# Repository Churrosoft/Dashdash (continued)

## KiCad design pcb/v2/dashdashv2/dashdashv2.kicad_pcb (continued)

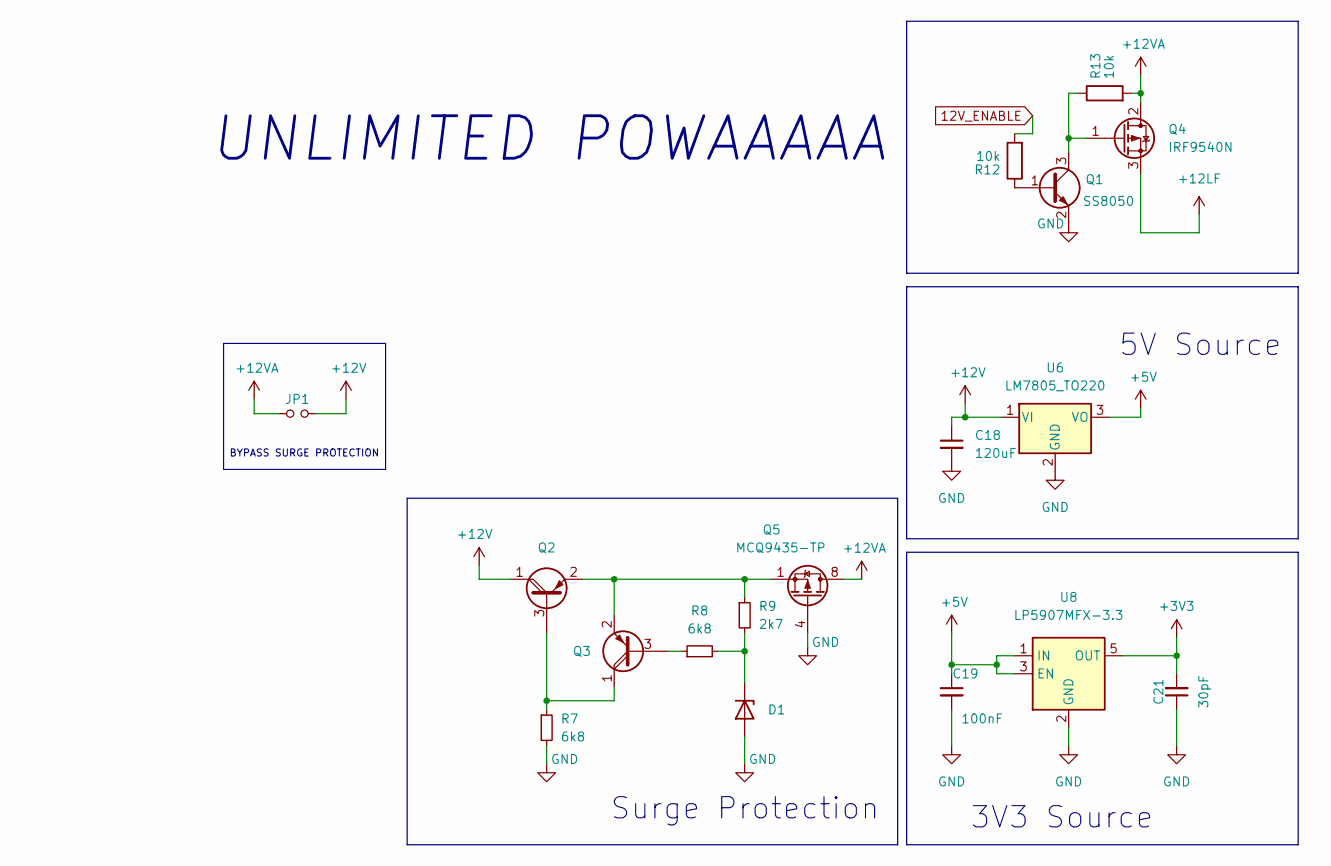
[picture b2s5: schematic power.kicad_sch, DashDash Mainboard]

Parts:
C18: 120uF; CP_Elec_8x6.5
C19: 100nF; C_0603_1608Metric
C21: 30pF; C_0603_1608Metric
D1: BZX84C5V6LT1G; SOT-23
JP1: Jumper_NO_Small; SolderJumper-2_P1.3mm_Open_RoundedPad1.0x1.5mm
Q1: SS8050; SOT-23; LCSC C2150
Q2, Q3: 2PB1424,115; SOT-89-3
Q4: IRF9540N; TO-252-2
Q5: MCQ9435-TP; SOIC-8_3.9x4.9mm_P1.27mm
R7, R8: 6k8; R_0603_1608Metric
R9: 2k7; R_0603_1608Metric
R12, R13: 10k; R_0603_1608Metric
U6: LM7805_TO220; TO-220-3_Vertical
U8: LP5907MFX-3.3; SOT-23-5

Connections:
12V_BATT: JP1.1, Q4.2 (D), Q5.5 (D), Q5.6 (D), Q5.7 (D), Q5.8 (D), R13.2; also elsewhere on the board
12V_ENABLE: R12.2; also elsewhere on the board
+3V3: C21.2, U8.5 (OUT); also elsewhere on the board
+5V: C19.1, U6.3 (VO), U8.1 (IN), U8.3 (EN); also elsewhere on the board
+12LF: Q4.3 (S); also elsewhere on the board
+12V: C18.1, JP1.2, Q2.1 (C), U6.1 (VI); also elsewhere on the board
GND: C18.2, C19.2, C21.1, D1.1 (A), Q1.2 (E), Q5.4 (G), R7.2, U6.2 (GND), U8.2 (GND); also elsewhere on the board
unnamed: D1.3 (K), R8.2, R9.2
unnamed: Q1.1 (B), R12.1
unnamed: Q1.3 (C), Q4.1 (G), R13.1
unnamed: Q2.2 (E), Q3.2 (E), Q5.1 (S), Q5.2 (S), Q5.3 (S), R9.1
unnamed: Q2.3 (B), Q3.1 (C), R7.1
unnamed: Q3.3 (B), R8.1

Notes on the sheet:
BYPASS SURGE PROTECTION
UNLIMITED POWAAAAA
5V Source
Surge Protection
3V3 Source

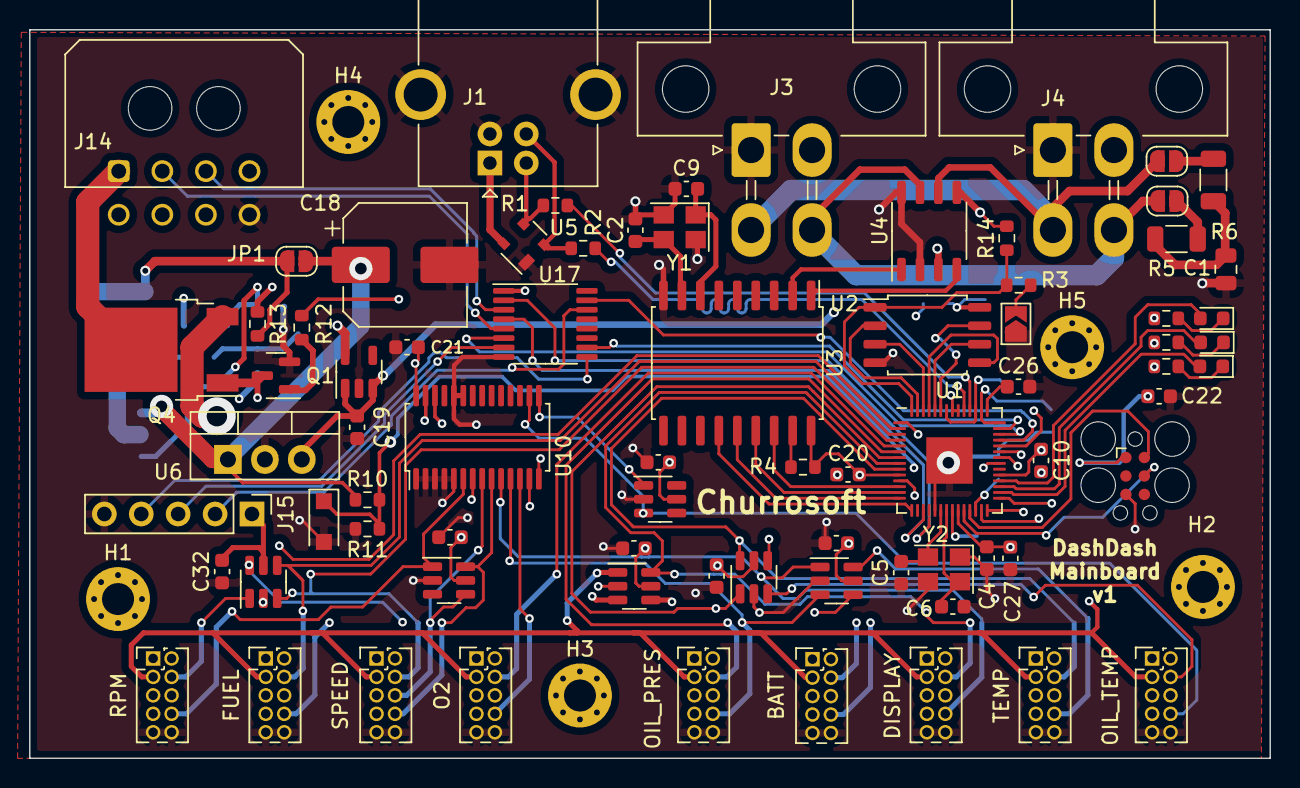
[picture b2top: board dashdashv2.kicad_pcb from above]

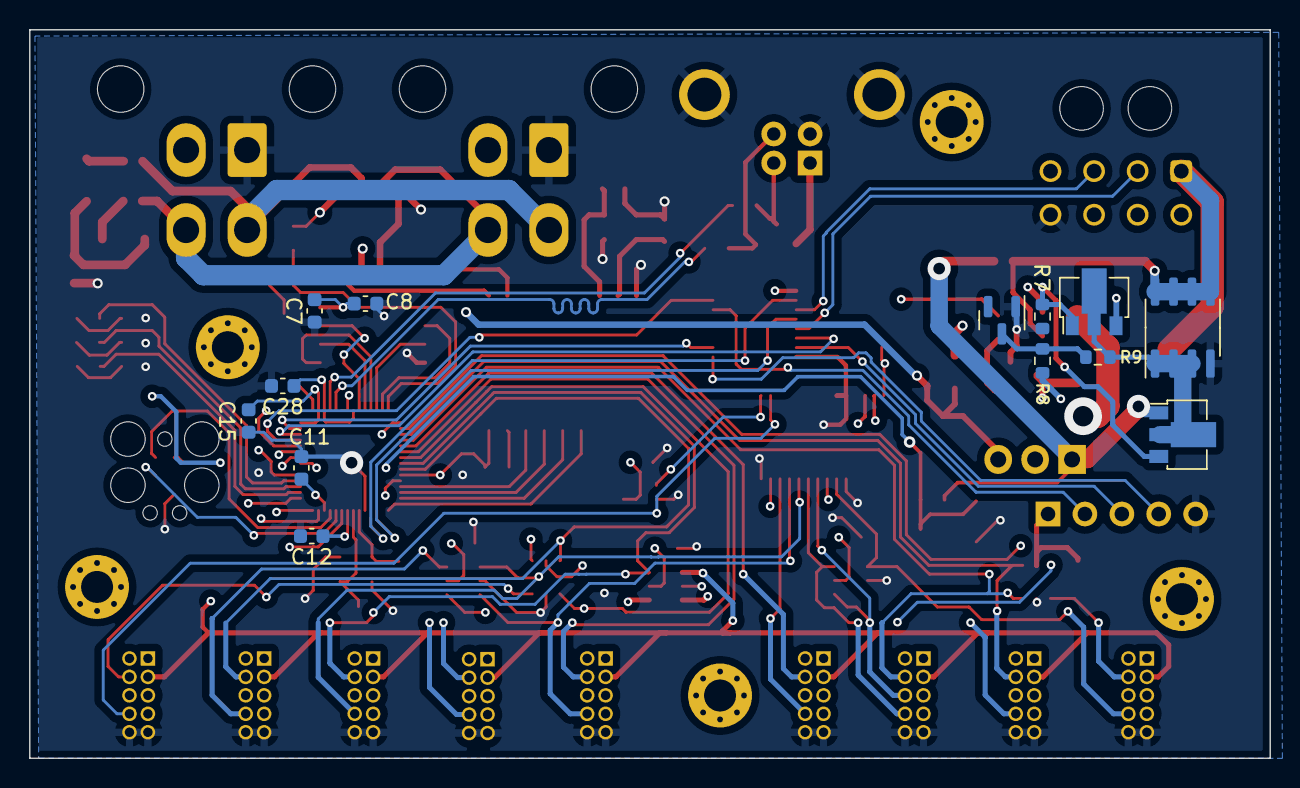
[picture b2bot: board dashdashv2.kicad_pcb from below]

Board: 4 copper layers, 85.4 x 50.1 mm, 94 parts (13 on the bottom side), 86 nets.

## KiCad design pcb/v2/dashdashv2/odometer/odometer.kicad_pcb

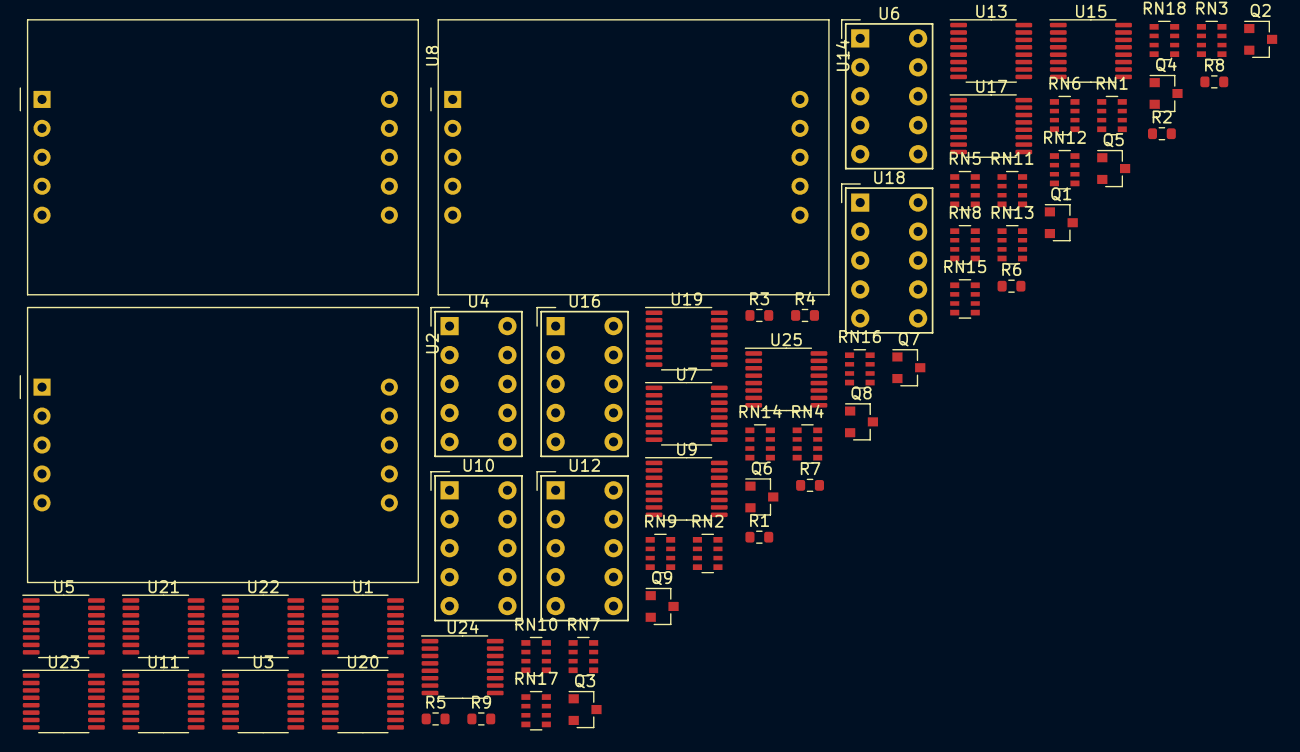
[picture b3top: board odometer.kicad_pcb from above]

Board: 2 copper layers, 61 parts (0 on the bottom side), 210 nets, no tracks yet.

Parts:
Q1, Q2, Q3, Q4, Q5, Q6, Q7, Q8, Q9: BSS138; SOT-23
R1, R2, R3, R4, R5, R6, R7, R8, R9: 1k 1/10W +-1%; R_0603_1608Metric
RN1, RN2, RN3, RN4, RN5, RN6, RN7, RN8, RN9, RN10, RN11, RN12, RN13, RN14, RN15, RN16, RN17, RN18: 560Ω ±5% 63mW; R_Array_Convex_4x0603
U1, U3, U5, U7, U9, U11, U13, U15, U17: 4511; TSSOP-16_4.4x5mm_P0.65mm
U2, U8, U14: HDSP-7801; SA15-11xxx
U4, U6, U10, U12, U16, U18: HDSP-7801
U19, U20, U21, U22, U23, U24, U25: 74HC595; TSSOP-16_4.4x5mm_P0.65mm

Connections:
+12V: U1.16 (Vdd), U3.16 (Vdd), U5.16 (Vdd), U7.16 (Vdd), U9.16 (Vdd), U11.16 (Vdd), U13.16 (Vdd), U15.16 (Vdd), U17.16 (Vdd), U19.16 (VCC), U20.16 (VCC), U21.16 (VCC), U22.16 (VCC), U23.16 (VCC), U24.16 (VCC), U25.16 (VCC)
/OE: U19.13 (~OE), U20.13 (~OE), U21.13 (~OE), U22.13 (~OE), U23.13 (~OE), U24.13 (~OE), U25.13 (~OE)
/PWM_OD: R2.1, R3.1, R5.1, R6.1, R8.1, R9.1
/PWM_VEL: R1.1, R4.1, R7.1
/RCLK: U19.12 (RCLK), U20.12 (RCLK), U21.12 (RCLK), U22.12 (RCLK), U23.12 (RCLK), U24.12 (RCLK), U25.12 (RCLK)
/SER: U19.9 (QH'), U19.14 (SER), U20.9 (QH'), U20.14 (SER), U21.9 (QH'), U21.14 (SER), U22.9 (QH'), U22.14 (SER), U23.9 (QH'), U23.14 (SER), U24.9 (QH'), U24.14 (SER), U25.14 (SER)
/SRCLK: U19.11 (SRCLK), U20.11 (SRCLK), U21.11 (SRCLK), U22.11 (SRCLK), U23.11 (SRCLK), U24.11 (SRCLK), U25.11 (SRCLK)
/SRCLR: U19.10 (~SRCLR), U20.10 (~SRCLR), U21.10 (~SRCLR), U22.10 (~SRCLR), U23.10 (~SRCLR), U24.10 (~SRCLR), U25.10 (~SRCLR)
/S_7S_A_BI: U1.4 (~BI), U24.1 (QB)
/S_7S_A_DA: U1.7 (DA), U23.4 (QE)
/S_7S_A_DB: U1.1 (DB), U23.5 (QF)
/S_7S_A_DC: U1.2 (DC), U23.6 (QG)
/S_7S_A_DD: U1.6 (DD), U23.7 (QH)
/S_7S_A_LT: U1.3 (~LT), U24.15 (QA)
/S_7S_B_BI: U7.4 (~BI), U13.4 (~BI), U24.7 (QH), U25.5 (QF)
/S_7S_B_DA: U7.7 (DA), U13.7 (DA), U24.2 (QC), U25.15 (QA)
/S_7S_B_DB: U7.1 (DB), U13.1 (DB), U24.3 (QD), U25.1 (QB)
/S_7S_B_DC: U7.2 (DC), U13.2 (DC), U24.4 (QE), U25.2 (QC)
/S_7S_B_DD: U7.6 (DD), U13.6 (DD), U24.5 (QF), U25.3 (QD)
/S_7S_B_LT: U7.3 (~LT), U13.3 (~LT), U24.6 (QG), U25.4 (QE)
/S_7S_D_1_A: U15.7 (DA), U19.15 (QA)
/S_7S_D_1_B: U15.1 (DB), U19.1 (QB)
/S_7S_D_1_BI: U15.4 (~BI), U19.5 (QF)
/S_7S_D_1_C: U15.2 (DC), U19.2 (QC)
/S_7S_D_1_D: U15.6 (DD), U19.3 (QD)
/S_7S_D_1_LT: U15.3 (~LT), U19.4 (QE)
/S_7S_D_2_A: U5.7 (DA), U19.6 (QG)
/S_7S_D_2_B: U5.1 (DB), U19.7 (QH)
/S_7S_D_2_BI: U5.4 (~BI), U20.3 (QD)
/S_7S_D_2_C: U5.2 (DC), U20.15 (QA)
/S_7S_D_2_D: U5.6 (DD), U20.1 (QB)
/S_7S_D_2_LT: U5.3 (~LT), U20.2 (QC)
/S_7S_D_3_A: U3.7 (DA), U20.4 (QE)
/S_7S_D_3_B: U3.1 (DB), U20.5 (QF)
/S_7S_D_3_BI: U3.4 (~BI), U21.1 (QB)
/S_7S_D_3_C: U3.2 (DC), U20.6 (QG)
/S_7S_D_3_D: U3.6 (DD), U20.7 (QH)
/S_7S_D_3_LT: U3.3 (~LT), U21.15 (QA)
/S_7S_D_4_A: U9.7 (DA), U21.2 (QC)
/S_7S_D_4_B: U9.1 (DB), U21.3 (QD)
/S_7S_D_4_BI: U9.4 (~BI), U21.7 (QH)
/S_7S_D_4_C: U9.2 (DC), U21.4 (QE)
/S_7S_D_4_D: U9.6 (DD), U21.5 (QF)
/S_7S_D_4_LT: U9.3 (~LT), U21.6 (QG)
/S_7S_D_5_A: U11.7 (DA), U22.15 (QA)
/S_7S_D_5_B: U11.1 (DB), U22.1 (QB)
/S_7S_D_5_BI: U11.4 (~BI), U22.5 (QF)
/S_7S_D_5_C: U11.2 (DC), U22.2 (QC)
/S_7S_D_5_D: U11.6 (DD), U22.3 (QD)
/S_7S_D_5_LT: U11.3 (~LT), U22.4 (QE)
/S_7S_D_6_A: U17.7 (DA), U22.6 (QG)
/S_7S_D_6_B: U17.1 (DB), U22.7 (QH)
/S_7S_D_6_BI: U17.4 (~BI), U23.3 (QD)
/S_7S_D_6_C: U17.2 (DC), U23.15 (QA)
/S_7S_D_6_D: U17.6 (DD), U23.1 (QB)
/S_7S_D_6_LT: U17.3 (~LT), U23.2 (QC)
GND: Q1.2 (S), Q2.2 (S), Q3.2 (S), Q4.2 (S), Q5.2 (S), Q6.2 (S), Q7.2 (S), Q8.2 (S), Q9.2 (S), RN11.8 (R1.2), U1.5 (~EL), U1.8 (Vss), U3.5 (~EL), U3.8 (Vss), U5.5 (~EL), U5.8 (Vss), U7.5 (~EL), U7.8 (Vss), U9.5 (~EL), U9.8 (Vss), U11.5 (~EL), U11.8 (Vss), U13.5 (~EL), U13.8 (Vss), U15.5 (~EL), U15.8 (Vss), U17.5 (~EL), U17.8 (Vss), U19.8 (GND), U20.8 (GND), U21.8 (GND), U22.8 (GND), U23.8 (GND), U24.8 (GND), U25.8 (GND)
unnamed: Q1.1 (G), R1.2
unnamed: Q1.3 (D), U2.1 (CA), U2.6 (CA)
unnamed: Q2.1 (G), R2.2
unnamed: Q2.3 (D), U4.1 (CA), U4.6 (CA)
unnamed: Q3.1 (G), R3.2
unnamed: Q3.3 (D), U6.1 (CA), U6.6 (CA)
unnamed: Q4.1 (G), R4.2
unnamed: Q4.3 (D), U8.1 (CA), U8.6 (CA)
unnamed: Q5.1 (G), R5.2
unnamed: Q5.3 (D), U10.1 (CA), U10.6 (CA)
unnamed: Q6.1 (G), R6.2
unnamed: Q6.3 (D), U12.1 (CA), U12.6 (CA)
unnamed: Q7.1 (G), R7.2
unnamed: Q7.3 (D), U14.1 (CA), U14.6 (CA)
unnamed: Q8.1 (G), R8.2
unnamed: Q8.3 (D), U16.1 (CA), U16.6 (CA)
unnamed: Q9.1 (G), R9.2
unnamed: Q9.3 (D), U18.1 (CA), U18.6 (CA)
unnamed: RN1.1 (R1.1), U2.5 (D)
unnamed: RN1.2 (R2.1), U2.8 (C)
unnamed: RN1.3 (R3.1), U2.9 (B)
unnamed: RN1.4 (R4.1), U2.10 (A)
unnamed: RN1.5 (R4.2), U1.13 (Qa)
unnamed: RN1.6 (R3.2), U1.12 (Qb)
unnamed: RN1.7 (R2.2), U1.11 (Qc)
unnamed: RN1.8 (R1.2), U1.10 (Qd)
unnamed: RN2.1 (R1.1), U4.5 (D)
unnamed: RN2.2 (R2.1), U4.8 (C)
unnamed: RN2.3 (R3.1), U4.9 (B)
unnamed: RN2.4 (R4.1), U4.10 (A)
unnamed: RN2.5 (R4.2), U3.13 (Qa)
unnamed: RN2.6 (R3.2), U3.12 (Qb)
unnamed: RN2.7 (R2.2), U3.11 (Qc)
unnamed: RN2.8 (R1.2), U3.10 (Qd)
unnamed: RN3.1 (R1.1), U6.5 (D)
unnamed: RN3.2 (R2.1), U6.8 (C)
unnamed: RN3.3 (R3.1), U6.9 (B)
unnamed: RN3.4 (R4.1), U6.10 (A)
unnamed: RN3.5 (R4.2), U5.13 (Qa)
unnamed: RN3.6 (R3.2), U5.12 (Qb)
unnamed: RN3.7 (R2.2), U5.11 (Qc)
unnamed: RN3.8 (R1.2), U5.10 (Qd)
unnamed: RN4.1 (R1.1), U2.7 (DP)
unnamed: RN4.2 (R2.1), U2.3 (G)
unnamed: RN4.3 (R3.1), U2.2 (F)
unnamed: RN4.4 (R4.1), U2.4 (E)
unnamed: RN4.5 (R4.2), U1.9 (Qe)
unnamed: RN4.6 (R3.2), U1.15 (Qf)
unnamed: RN4.7 (R2.2), U1.14 (Qg)
unnamed: RN5.1 (R1.1), U4.7 (DP)
unnamed: RN5.2 (R2.1), U4.3 (G)
unnamed: RN5.3 (R3.1), U4.2 (F)
unnamed: RN5.4 (R4.1), U4.4 (E)
unnamed: RN5.5 (R4.2), U3.9 (Qe)
unnamed: RN5.6 (R3.2), U3.15 (Qf)
unnamed: RN5.7 (R2.2), U3.14 (Qg)
unnamed: RN6.1 (R1.1), U6.7 (DP)
unnamed: RN6.2 (R2.1), U6.3 (G)
unnamed: RN6.3 (R3.1), U6.2 (F)
unnamed: RN6.4 (R4.1), U6.4 (E)
unnamed: RN6.5 (R4.2), U5.9 (Qe)
unnamed: RN6.6 (R3.2), U5.15 (Qf)
unnamed: RN6.7 (R2.2), U5.14 (Qg)
unnamed: RN7.1 (R1.1), U8.5 (D)
unnamed: RN7.2 (R2.1), U8.8 (C)
unnamed: RN7.3 (R3.1), U8.9 (B)
unnamed: RN7.4 (R4.1), U8.10 (A)
unnamed: RN7.5 (R4.2), U7.13 (Qa)
unnamed: RN7.6 (R3.2), U7.12 (Qb)
unnamed: RN7.7 (R2.2), U7.11 (Qc)
unnamed: RN7.8 (R1.2), U7.10 (Qd)
unnamed: RN8.1 (R1.1), U10.5 (D)
unnamed: RN8.2 (R2.1), U10.8 (C)
unnamed: RN8.3 (R3.1), U10.9 (B)
unnamed: RN8.4 (R4.1), U10.10 (A)
unnamed: RN8.5 (R4.2), U9.13 (Qa)
unnamed: RN8.6 (R3.2), U9.12 (Qb)
unnamed: RN8.7 (R2.2), U9.11 (Qc)
unnamed: RN8.8 (R1.2), U9.10 (Qd)
unnamed: RN9.1 (R1.1), U12.5 (D)
unnamed: RN9.2 (R2.1), U12.8 (C)
unnamed: RN9.3 (R3.1), U12.9 (B)
unnamed: RN9.4 (R4.1), U12.10 (A)
unnamed: RN9.5 (R4.2), U11.13 (Qa)
unnamed: RN9.6 (R3.2), U11.12 (Qb)
unnamed: RN9.7 (R2.2), U11.11 (Qc)
unnamed: RN9.8 (R1.2), U11.10 (Qd)
unnamed: RN10.1 (R1.1), U8.7 (DP)
unnamed: RN10.2 (R2.1), U8.3 (G)
unnamed: RN10.3 (R3.1), U8.2 (F)
unnamed: RN10.4 (R4.1), U8.4 (E)
unnamed: RN10.5 (R4.2), U7.9 (Qe)
unnamed: RN10.6 (R3.2), U7.15 (Qf)
unnamed: RN10.7 (R2.2), U7.14 (Qg)
unnamed: RN11.1 (R1.1), U10.7 (DP)
unnamed: RN11.2 (R2.1), U10.3 (G)
unnamed: RN11.3 (R3.1), U10.2 (F)
unnamed: RN11.4 (R4.1), U10.4 (E)
unnamed: RN11.5 (R4.2), U9.9 (Qe)
unnamed: RN11.6 (R3.2), U9.15 (Qf)
unnamed: RN11.7 (R2.2), U9.14 (Qg)
unnamed: RN12.1 (R1.1), U12.7 (DP)
unnamed: RN12.2 (R2.1), U12.3 (G)
unnamed: RN12.3 (R3.1), U12.2 (F)
unnamed: RN12.4 (R4.1), U12.4 (E)
unnamed: RN12.5 (R4.2), U11.9 (Qe)
unnamed: RN12.6 (R3.2), U11.15 (Qf)
unnamed: RN12.7 (R2.2), U11.14 (Qg)
unnamed: RN13.1 (R1.1), U14.5 (D)
unnamed: RN13.2 (R2.1), U14.8 (C)
unnamed: RN13.3 (R3.1), U14.9 (B)
unnamed: RN13.4 (R4.1), U14.10 (A)
unnamed: RN13.5 (R4.2), U13.13 (Qa)
unnamed: RN13.6 (R3.2), U13.12 (Qb)
unnamed: RN13.7 (R2.2), U13.11 (Qc)
unnamed: RN13.8 (R1.2), U13.10 (Qd)
unnamed: RN14.1 (R1.1), U16.5 (D)
unnamed: RN14.2 (R2.1), U16.8 (C)
unnamed: RN14.3 (R3.1), U16.9 (B)
unnamed: RN14.4 (R4.1), U16.10 (A)
unnamed: RN14.5 (R4.2), U15.13 (Qa)
unnamed: RN14.6 (R3.2), U15.12 (Qb)
unnamed: RN14.7 (R2.2), U15.11 (Qc)
unnamed: RN14.8 (R1.2), U15.10 (Qd)
unnamed: RN15.1 (R1.1), U18.5 (D)
unnamed: RN15.2 (R2.1), U18.8 (C)
unnamed: RN15.3 (R3.1), U18.9 (B)
unnamed: RN15.4 (R4.1), U18.10 (A)
unnamed: RN15.5 (R4.2), U17.13 (Qa)
unnamed: RN15.6 (R3.2), U17.12 (Qb)
unnamed: RN15.7 (R2.2), U17.11 (Qc)
unnamed: RN15.8 (R1.2), U17.10 (Qd)
unnamed: RN16.1 (R1.1), U14.7 (DP)
unnamed: RN16.2 (R2.1), U14.3 (G)
unnamed: RN16.3 (R3.1), U14.2 (F)
unnamed: RN16.4 (R4.1), U14.4 (E)
unnamed: RN16.5 (R4.2), U13.9 (Qe)
unnamed: RN16.6 (R3.2), U13.15 (Qf)
unnamed: RN16.7 (R2.2), U13.14 (Qg)
unnamed: RN17.1 (R1.1), U16.7 (DP)
unnamed: RN17.2 (R2.1), U16.3 (G)
unnamed: RN17.3 (R3.1), U16.2 (F)
unnamed: RN17.4 (R4.1), U16.4 (E)
unnamed: RN17.5 (R4.2), U15.9 (Qe)
unnamed: RN17.6 (R3.2), U15.15 (Qf)
unnamed: RN17.7 (R2.2), U15.14 (Qg)
unnamed: RN18.1 (R1.1), U18.7 (DP)
unnamed: RN18.2 (R2.1), U18.3 (G)
unnamed: RN18.3 (R3.1), U18.2 (F)
unnamed: RN18.4 (R4.1), U18.4 (E)
unnamed: RN18.5 (R4.2), U17.9 (Qe)
unnamed: RN18.6 (R3.2), U17.15 (Qf)
unnamed: RN18.7 (R2.2), U17.14 (Qg)
